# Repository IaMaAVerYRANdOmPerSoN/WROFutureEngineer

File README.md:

# WRO 2026 Future Engineers – TEAM APOSTLA

## Project Overview
This repository contains the complete documentation, code, design files, and test records for our **WRO 2026 Future Engineers** self-driving car project.

This repo is organized to show:
- how our robot is mechanically designed
- how power and sensors are arranged
- how the software is structured
- how engineering decisions were made
- how another team could reproduce the robot

---

## Team Members

<p align="center"><i>Explorer Robotics — WRO Future Engineers 2026</i></p>

---

We are a three-person team from Explorer Robotics in Whitby, Ontario, Canada. We have been competing in WRO for several years. This year we set out to build a fully autonomous self-driving robot from scratch, designing our own chassis, differential gear system, and vision pipeline.

## Elvis Wang
<table>
<tr>
  <td align="center" width="40%">
    <br>
    <em>Elvis</em>
  </td>

  <td valign="top" width="60%">

  ### Information
  - *I love building!!!!!!!*
  - 15 years old
  - Hi, my name is Elvis. I'm 15. I enjoy building and 3D modeling various objects with Fusion 360. I've been with Explorer Robotics ever since I was 8 years old.
  </td>
</tr>
</table>

---

## Michael Xie
<table>
<tr>
  <td align="center" width="40%">
    <br>
    <em>Michael</em>
  </td>

  <td valign="top" width="60%">

  ### Information
  - *I love coding!!!!!!*
  - 14 years old
  - I'm Michael. I'm 14, love coding and solving problems. I've been involved in WRO for several years and enjoy using my programming skills to help our team build and improve our robot.
  </td>
</tr>
</table>

---

## Ryan Rao
<table>
<tr>
  <td align="center" width="40%">
    <br>
    <em>Ryan</em>
  </td>

  <td valign="top" width="60%">

  ### Information
  - *I love dogs*
  - 15 years old
  - Hi! I'm Ryan. I'm 15, love to write, play badminton, listen to music, and travel. I've been involved in robotics for nearly a decade and participated in both FLL and WRO Robo Mission.
  </td>
</tr>
</table>

## Coach Rice
<table>
<tr>
  <td align="center" width="40%">
    <br>
    <em>Coach Rice</em>
  </td>

  <td valign="top" width="60%">

  ### Information
  - Head coach of Robotics Competitions, including FLL (First LEGO League),  WRO (World Robotics Olympiad) Robo Sports, Future Engineers, and Robo Mission. Led teams in winning multiple national, international robotics, and programming awards.
  - Over 20 years of IT industry experience as a software engineer working internationally.
  - MSc in Electrical & Computer Engineering from the University of Alberta.
  - BSc in Mathematics from Peking University.
  - Founder of Explorer Robotics, a local robotics club in Ajax and Whitby, teaching coding, AI, robotics, etc.
  </td>
</tr>
</table>

---

## Robot Summary

> Our robot is a self-driving car built for the WRO 2026 Future Engineers challenge. It uses one downward-angled camera to spot track walls, corner lines, and colored obstacle pillars, and follows the track using a state-machine control loop. The robot runs on a Raspberry Pi 5 for vision, an Arduino Nano for motor and servo control, a Furitek Micro Komodo 1212 brushless motor that drives the rear wheels through a differential gearbox, and rack-and-pinion steering run by an HS-5055MG servo. Our design is simple and reliable, using one sensor for all detection and a sturdy build that's easy to fix during competition.

---

## Journal
- [View Journal](docs/journal/CHANGELOG.md)
- [View Journal PDF](docs/journal/CHANGELOG.pdf)

---

## Table of Contents

- [Project Overview](#project-overview)
- [Team Members](#team-members)
- [Robot Summary](#robot-summary)
- [Repository Structure](#repository-structure)
  - [Main Files](#main-files)
  - [Documentation](#documentation)
  - [Other Project Assets](#other-project-assets)
- [1. Mechanical Design](#1-mechanical-design)
  - [Images of Robot](#images-of-robot)
  - [Structural Design](#structural-design)
    - [Old Design](#old-design)
    - [Improvements](#improvements)
    - [Changes](#changes)
  - [3D Printed Parts](#3d-printed-parts)
  - [Full Robot](#full-robot)
- [2. Power and Sensor Architecture](#2-power-and-sensor-architecture)
  - [Power](#power)
  - [Voltage and Current Requirements](#voltage-and-current-requirements)
    - [5V Rail (Raspberry Pi, Arduino, Servo)](#5v-rail-raspberry-pi-arduino-servo)
    - [7.4V Rail (Motor)](#74v-rail-motor)
    - [Total Battery Power and Current](#total-battery-power-and-current)
    - [Runtime Estimate](#runtime-estimate)
  - [Sensors](#sensors)
  - [Compute](#compute)
  - [Summary](#summary)
- [3. Software Architecture and Strategy](#3-software-architecture-and-strategy)
  - [Software](#software)
  - [Architecture](#architecture)
  - [Config](#config)
  - [Vision](#vision)
    - [Wall Following](#wall-following)
    - [Obstacle Detection](#obstacle-detection)
  - [Hardware Interfaces](#hardware-interfaces)
  - [Challenge Running](#challenge-running)
    - [Open Challenge](#open-challenge)
    - [Obstacle Challenge](#obstacle-challenge)
  - [Running the Robot](#running-the-robot)
- [4. Systems Engineering and Design Decisions](#4-systems-engineering-and-design-decisions)
  - [Constraints](#constraints)
  - [Trade-offs](#trade-offs)
  - [Design Iteration](#design-iteration)
  - [Risk Analysis](#risk-analysis)
  - [Subsystem Interactions](#subsystem-interactions)
  - [Summary](#summary-1)
- [5. Reproducibility](#5-reproducibility)
  - [Software Setup](#software-setup)
  - [Hardware Setup](#hardware-setup)
  - [Testing](#testing)
  - [Summary](#summary-2)
- [Testing and Validation](#testing-and-validation)
- [Media and Visual Documentation](#media-and-visual-documentation)
  - [Diagrams](#diagrams)
  - [Videos](#videos)
- [CAD and Wiring Files](#cad-and-wiring-files)
- [Version History](#version-history)
- [Contribution and Documentation Rules](#contribution-and-documentation-rules)
- [Final Notes](#final-notes)
- [View Journal](docs/journal/CHANGELOG.md)

---
### GitHub Releases
[GitHub releases page](https://github.com/IaMaAVerYRANdOmPerSoN/WROFutureEngineer/releases/tag/v0.1.0)
- Source Code
- Cad File

---

## Repository Structure

### Main Files
- `README.md` – main project overview and navigation
- `LICENSE` – repository license
- `.gitignore` – ignored local/generated files
- `requirements.txt` – Python dependencies

### Documentation
- `docs/01_mechanical/` – mobility and mechanical design
- `docs/02_power_sensors/` – power system and sensor architecture
- `docs/03_software/` – software design and obstacle strategy
- `docs/04_systems_engineering/` – engineering decisions, trade-offs, and risks
- `docs/05_reproducibility/` – build, setup, assembly, and testing workflow
- `docs/journal/` – dated engineering journal (Markdown + PDF export)
- `docs/img/` – images referenced throughout the docs (robot photos, diagrams, team photos)
- `docs/plan.md`, `docs/shoppingList.md`, `docs/coach_comments.md` – supporting planning docs

**Other top-level folders:**
- `ArudinoServer/` – PlatformIO firmware for the Arduino (low-level motor/servo control)
- `PiClient/` – Python code on the Raspberry Pi
    - `src/` – main vision processing, control, and Arduino communication logic
    - `src_min/` – a minimal/leaner variant of the same modules
    - `utils/tools/` – standalone calibration and debug tools (contours, manual control)
    - `tests/` – test and experiment scripts
- `EDA/` – KiCad PCB project 
    - `FAB/` – fabrication outputs (Gerbers, BOM, pick-and-place positions)
    - `lib/` – imported component symbol/footprint libraries

---

# 1. Mechanical Design
This section explains the physical design of the robot, including chassis layout, steering, drivetrain, torque/speed reasoning, and mechanical improvements over time.

---

### Files
- [`docs/mechanical/mechanical_reasoning.md`](docs/01_mechanical/mechanical_reasoning.md)
- [`docs/mechanical/mechanical_iterations.md`](docs/01_mechanical/mechanical_iterations.md)
- [`docs/mechanical/torque_speed_reasoning.md`](docs/01_mechanical/torque_speed_reasoning.md)

---

- **Dimentions**: 24cm length 10cm wide 28cm high
    - [Dimentions reasoning](docs/01_mechanical/mechanical_reasoning.md#size-reasoning)
- **Drive Motor**: Furitek Micro Komodo 1212 Stepper Motor
    - [Motor reasoning](docs/01_mechanical/mechanical_reasoning.md#motor-selectionmotor-selection)
- **Steering Motor**: HS-5055MG 11.9g Metal Gear Digital Micro Servo
    - [Steering reasoning](docs/01_mechanical/mechanical_reasoning.md#servo-motor)

### Images of Robot
| | |
|:---:|:---:|
|  |  |
|  |  |
|  |  |

---

- **Drive System**: We use rear wheel drive, means the motor's power is transmitted to the back wheels rather than the front.
    - [Why RWD?](docs/01_mechanical/mechanical_reasoning.md#drive-system)
- **Steering type:** Parallel (Zero-Ackermann), Both front wheels turn at the same angle instead of the inner wheel turning more sharply than the outer. It does cause slight tire scrub during turns but it is acceptable on a small lightweight robot on a smooth mat.
    - [Why Parallel Zero-Ackermann?](docs/01_mechanical/mechanical_reasoning.md#steering-system)
### Structural Design
To get our current design, we took inspiration from our previous robot we used last year in Future Engineers.

#### Old Design

#### Improvements
- Make the robot thinner for more clearence and better weight distribution
- More supports on the sides of the robot (we only had 2)

---

#### Changes
- Rotating the Raspiberry Pi 90 degrees would allow for a slimmer design
- Implimenting more supports on the sides of the robot
- We use the Arduino Nano instead of Hiwonder
- Changed the camera angle and added a place for the stepdown voltage

### 3D Printed Parts

- **Turning System**: Servo-actuated rack and pinion steering with a curved front bumper for wall sliding in the obstacle challenge. The servo connects to the steering rack via a servo horn and tie rods, rotating the servo horn pushes or pulls the tie rods, which turn the front wheels left or right.
    - [Turning system iterations](docs/01_mechanical/mechanical_iterations.md#turning-system)

- **Raspberry Pi 5 Layout, Camera Mount, and ESC**: Slim rotated design with a separated camera tower angled at 35 degrees downward. The ESC is mounted inside the same assembly to keep electronics consolidated.
    - [RP5 layout and camera mount iterations](docs/01_mechanical/mechanical_iterations.md#raspberry-pi-5-layout-and-camera-mount)

- **Arduino Nano Layout**: Main chassis plate holding the Arduino, servo, and front assembly; redesigned for compactness across four versions
    - [Arduino layout iterations](docs/01_mechanical/mechanical_iterations.md#europe-design)

- **Connectors**: 3D printed C-shaped connectors replacing brass standoffs to speed up assembly and disassembly
    - [Connector iterations](docs/01_mechanical/mechanical_iterations.md#connectors)

- **Furitek Micro Komodo 1212**: Brushless motor rated at 3450 KV and 120W; drives the rear wheels through the differential gearbox
    - [Motor reasoning](docs/01_mechanical/mechanical_reasoning.md#motor-selection)

- **Differential Gear System**: Custom-designed differential allowing the rear wheels to spin at different speeds during turns; went through multiple iterations before settling on an off-the-shelf gearbox

- **Wheels**: 35mm rubber wheels chosen to raise the chassis to give the differential adequate ground clearance
    - [Wheel and torque reasoning](docs/01_mechanical/torque_speed_reasoning.md)

- **Ball Bearings**: Four 6mm ball bearings pressed into the rear body mount to support the axles and reduce friction

---

### Full Robot

| | |
|:---:|:---:|
|  |

---

### Assembly Video

---

# 2. Power and Sensor Architecture
This section explains how the robot is powered, what sensors are used, where they are placed, and how they are calibrated.

### Files
- [`docs/02_power_sensors/power_architecture.md`](docs/02_power_sensors/power_architecture.md)
- [`docs/02_power_sensors/sensor_selection.md`](docs/02_power_sensors/sensor_selection.md)
- [`docs/02_power_sensors/sensor_placement.md`](docs/02_power_sensors/sensor_placement.md)
- [`docs/02_power_sensors/calibration.md`](docs/02_power_sensors/calibration.md)

---

### Power

Everything starts with a single Gens Ace 1300mAh 2S LiPo battery. From there, power splits into two separate paths so the compute side and the actuator side never interfere with each other.

The first path goes through our Yahboom voltage regulator board, which steps the battery's 7.4V down to a clean 5V. That 5V feeds into the Raspberry Pi 5 through USB-C. The Arduino Nano doesn't connect to the battery at all, it gets powered straight from the Pi over a USB-B cable. The camera is also powered off the Pi, through its flat CSI ribbon cable, which carries both data and power in one connector.

The second path runs through the ESC. The ESC takes power directly from the battery and has its own built-in BEC (battery eliminator circuit) to regulate it. On the output side, the ESC's voltage pin powers the servo, and the ESC also drives the brushless motor directly since the motor doesn't need to be stepped down first.

<p align="center"><i>Full electronics schematic showing power distribution and signal connections.</i></p>

The Raspberry Pi is the brain, it runs the vision pipeline, figures out where objects are, and decides what the robot should do next. The Arduino doesn't make any decisions, it just takes the drive commands the Pi sends it and turns them into precise PWM signals, since the Pi can't reliably time PWM output on its own while it's busy processing frames. The camera is the robot's only sense of the outside world, it feeds every frame the vision pipeline uses to find walls, corners, and pillars.

On the actuator side, the ESC handles throttle control for the drive motor based on the PWM signal it gets from the Arduino, and its BEC also acts as the power source for the servo, so the servo never has to touch the battery directly. The servo itself just turns the front wheels left and right based on the steering commands coming from the Arduino, and the motor is what actually moves the robot forward, spinning the rear wheels through the differential.

- **Battery**: Gens Ace 1300mAh 2S LiPo, 7.4V nominal, 45C discharge
    - [Battery details](docs/02_power_sensors/power_architecture.md#battery)
- **Voltage Regulation**: Yahboom regulator converts 7.4V to 5V for the Raspberry Pi; ESC built-in BEC powers the servo independently
    - [Regulator details](docs/02_power_sensors/power_architecture.md#design-rationale)
- **Main Power Switch**: Smaller switch installed on the main battery rail after the original 20A switch was replaced for easier integration
    - [Power design](docs/02_power_sensors/power_architecture.md#iterations)
- **Estimated Runtime**: ~17 minutes at average load; enough for ~5 full competition runs per charge

## Voltage and Current Requirements

### 5V Rail (Raspberry Pi, Arduino, Servo)

| Component | Current Draw |
|-----------|-------------|
| Raspberry Pi 5 | 2.40A |
| Arduino Nano | 0.05A |
| Servo Motor (stall) | 0.70A |
| Camera (OV5647) | 0.25A |
| **Total 5V current** | **3.40A** |

Power at 5V: 3.40A × 5V = **17W**

Accounting for regulator efficiency (80%):
17W ÷ 0.8 = **21.25W** needed from battery for the 5V rail.

---

### 7.4V Rail (Motor)

| Component | Current Draw |
|-----------|-------------|
| Drive Motor (average during run) | 3.50A |
| **Total motor current** | **3.50A** |

Power at 7.4V: 3.50A × 7.4V = **25.9W**

---

### Total Battery Power and Current

| Rail | Power |
|------|-------|
| 5V rail (via regulator) | 21.25W |
| Motor rail (direct) | 25.9W |
| **Total** | **47.15W** |

Total current from battery:
47.15W ÷ 7.4V = **6.37A**

---

### Runtime Estimate

6.37A average draw from a 1300mAh (1.3Ah) battery at 80% usable capacity:

(1.3Ah × 0.8) ÷ 6.37A = **~0.16 hours (~10 minutes)**

In practice the robot lasts significantly longer because:
- The motor draws far less than stall current at competition speeds (30-40% throttle)
- The Raspberry Pi rarely hits full load simultaneously with peak motor draw
- The servo is at stall current only momentarily during sharp turns
- The regulator efficiency is typically closer to 85-90% under real load

At realistic average loads (~4A total), the expected runtime is approximately **17 minutes**, sufficient for ~5 full competition runs per charge.

Because of the decently short battery life, we have had between 4-5 batteries.

---

### Sensors

- **Camera (OV5647)**: Detects walls, corner lines, and colored pillars via CSI-2 at 640x480 up to 62.50 fps
    - [Camera selection](docs/02_power_sensors/sensor_selection.md#camera--ov5647)
    - [Camera placement](docs/02_power_sensors/sensor_placement.md)
- **IMU**: Detects rotation and acceleration
    - [IMU purpose](docs/02_power_sensors/sensor_selection.md#camera--ov5647)
      
---

### Compute

- **Raspberry Pi 5 (8GB)**: Main compute unit running the vision pipeline, control loop, and Arduino communication
    - [Raspberry Pi details](docs/02_power_sensors/sensor_selection.md#raspberry-pi-5-8gb)
- **Arduino Nano**: Handles PWM output to ESC and servo; receives drive commands from the Pi over USB serial
    - [Arduino details](docs/02_power_sensors/sensor_selection.md#arduino-nano)

---

### Actuators

- **ESC**: Furitek Lizard Pro 30A/50A ESC
    - [ESC reasoning](docs/02_power_sensors/power_architecture.md#electronic-speed-controller)
- **Drive Motor**: Furitek Micro Komodo 1212 Stepper Motor
    - [Motor reasoning](docs/01_mechanical/mechanical_reasoning.md#motor-selectionmotor-selection)
- **Steering Motor**: HS-5055MG 11.9g Metal Gear Digital Micro Servo
    - [Steering reasoning](docs/01_mechanical/mechanical_reasoning.md#servo-motor)
---

## Risks and Mitigation

- **Voltage drop:** The 45C discharge rating minimizes voltage sag under peak current draw. Battery voltage is monitored during practice runs to identify cell degradation early.
- **Brownout:** The Pi is powered through a Yahboom voltage regulator board rather than directly from the battery, isolating it from motor-induced voltage dips. A regulator with sufficient headroom above the Pi's peak draw was selected. We may have broken one of our raspberry pi's because we forgot the regulator...
- **Electrical noise:** Motor and ESC wiring are routed away from signal wires. The serial communication lines between the Pi and Arduino are kept short.
- **Loose connectors:** All connectors are secured with heat shrink. Once, one of our wires got caught in the gear system causing damage, leading to a short circuit. All wiring has since been replaced.
- **Overheating:** The ESC and motor are mounted with airflow clearance. Competition runs are under 3 minutes, well within thermal limits. The Raspberry Pi fan is configured to always run after the temperature sensor proved unreliable on our unit.
- **Power spikes from motors / servos:** The ESC BEC powers the servo independently from the motor rail. The dedicated regulator for the Pi prevents motor spikes from reaching the compute system.

---

### Summary
- battery: Gens Ace 1300mAh 2S LiPo (7.4V, 45C)
- voltage regulation: Buck regulator for Pi (5V); ESC BEC for servo
- main sensors: OV5647 camera (CSI-2)
- sensor placement strategy: Camera mounted at front with downward tilt for field of view
- calibration approach: HSV color thresholds tuned under competition lighting using interactive tuning tools in `utils/`

---

# 3. Software Architecture and Strategy

## Software

This section explains the software that runs on the Raspberry Pi, including how the processes are structured, how the robot detects walls and obstacles, and how drive commands are sent to the Arduino.

---

### Files
- [`docs/03_software/architecture.md`](docs/03_software/architecture.md)
- [`docs/03_software/challenge)running.md`](docs/03_software/challenge_running.md)
- [`docs/03_software/config.md`](docs/03_software/config.md)
- [`docs/03_software/hardware_interfaces.md`](docs/03_software/hardware_interfaces.md)
- [`docs/03_software/state_machine.md`](docs/03_software/state_machine.md)
- [`docs/03_software/vision.md`](docs/03_software/vision.md)

---

## Architecture

Three processes run at the same time, camera, vision, and main control. The camera writes frames into shared memory, the vision process reads them and finds walls and obstacles, and the main process runs the state machine and sends commands to the Arduino. The system always uses the freshest data; stale frames and commands are dropped automatically.

- **Camera Process**: Captures frames and writes them into shared memory
    - [Architecture details](docs/03_software/architecture.md)
- **Vision Process**: Reads frames and finds walls and obstacles
    - [Vision details](docs/03_software/vision.md)
- **Main Process**: Runs the state machine and sends drive commands to the Arduino
    - [Runner details](docs/03_software/challenge_running.md)

<p align="center"><i>Full software architecture diagram.</i></p>

---

## Config

All settings are stored in `piclient.toml`. Nothing is hardcoded — speed, PD gains, HSV thresholds, serial ports, and ROI sizes are all in the config file. Once the robot starts, the config is locked and cannot be changed mid-run.

- **Settings file**: `piclient.toml` at the root of the repo
    - [Config details](docs/03_software/config.md)
- **Override priority**: CLI flag > environment variable > `piclient.toml` > code defaults

---

## Vision

### Wall Following

`open_challenge.py:95-104` the vision pipeline counts the number of black pixels in the left, right, and center regions of the image. The difference between right and left distance is fed into a PD controller (`wall_follow.tick(right - left)`), and the output is sent as a steering command via `client.drive_motors(...)`. If the right wall is further than the left, the correction steers left, and vice versa. It only cares about relative position, not absolute distance, which is why the perspective transform can be skipped. Camera distortion does not change which wall is closer.

### Obstacle Detection

`vision_processing.py:100-106`: red and green pillars are found the same way as walls, but contours (as NumPy arrays) are used instead of simple pixel counts. Once a pillar is found, `_get_target` calculates a target x position by offsetting the pillar's x position proportionally to the width of the pillar. A separate PD controller (`obstacle_avoid`) steers toward that target x position rather than centering between walls, while maintaining 20% wall-follow weight to keep general awareness. This only runs in `obstacle_challenge.py`'s "obstacle_avoid" state, and only when `obstacles` is non-empty. Otherwise, it falls back to plain wall following.

- **Open Challenge**: Counts black pixels in left, right, and center regions. More black pixels means the wall is closer. Corner detection triggers when the center region fills up.
    - [Open challenge vision details](docs/03_software/vision.md#open-challenge)
- **Obstacle Challenge**: Finds red and green pillars using HSV color detection and calculates an offset target x position to steer toward the gap between the pillar and the wall.
    - [Obstacle challenge vision details](docs/03_software/vision.md#obstacle-challenge)

---

## Hardware Interfaces

- **Camera**: Runs in its own process, writes frames directly into shared memory with no copying
    - [Camera details](docs/03_software/hardware_interfaces.md#camera)
- **Arduino Client**: Sends serial commands with transaction IDs so multiple commands can be in flight at once
    - [Arduino client details](docs/03_software/hardware_interfaces.md#arduino-client)
- **DriveCommandExecutor**: Sits between the control loop and the Arduino, only the latest command is sent, stale commands are thrown away
    - [DriveCommandExecutor details](docs/03_software/hardware_interfaces.md#drivecommandexecutor)

---

## Challenge Running
The robot uses a finite state machine (FSM) to decide what to do at any given moment. Each state has a specific trigger that causes the robot to enter it and a specific action it takes while in that state. The FSM runs once per camera frame, so the robot is constantly re-evaluating which state it should be in based on the latest vision data.

### Open Challenge

| State | Trigger | Action |
|-------|---------|--------|
| Straight | Default | Wall follow with PD controller |
| Turn | Black fill detected ahead | Hard steer toward missing wall |
| Final Turn | Last turn of last lap | Same as Turn |
| Final Straight | After final turn | Drive to stop |

- [Open challenge runner details](docs/03_software/challenge_running.md#open-challenge)

### Obstacle Challenge

| State | Trigger | Action |
|-------|---------|--------|
| Straight | Default | Wall follow with PD controller |
| Turn | Corner detected | Hard steer toward missing wall |
| Obstacle Avoid | Vision returns a pillar target | Steers toward the gap between pillar and wall |
| Parallel Parking | Vision returns a parking lot target and the 3rd lap is complete | Steers toward the parking lot and executes a parallel parking maneuver |

Same as the open challenge with one extra state. When a pillar is detected, the robot steers toward the gap between the pillar and the wall. Green pillars are passed on the left, red on the right.

- [Obstacle challenge runner details](docs/03_software/challenge_running.md#obstacle-challenge)

---

## Running the Robot

```bash
wro --GeneralConfig.CHALLENGE open
wro --GeneralConfig.CHALLENGE obstacle
```

Full auto-generated API docs: https://apostla-api-reference.web.app/
---

# 4. Systems Engineering and Design Decisions
This section explains how the robot was developed as an integrated system and how trade-offs were evaluated.

- **Engineering Journal**:
The journal is best viewed on GitHub where all links are clickable. A PDF version is also available for submission.
    - [View Journal](docs/journal/CHANGELOG.md)
    - [View Journal PDF](docs/journal/CHANGELOG.pdf)

### Files
- [`docs/04_systems_engineering/subsystem_interactions.md`](docs/04_systems_engineering/subsystem_interactions.md)
- [`docs/04_systems_engineering/constraints_tradeoffs.md`](docs/04_systems_engineering/constraints_tradeoffs.md)
- [`docs/04_systems_engineering/risk_analysis.md`](docs/04_systems_engineering/risk_analysis.md)
- [`docs/04_systems_engineering/iteration_cycles.md`](docs/04_systems_engineering/iteration_cycles.md)

### Constraints

The robot must satisfy four levels of constraints in order of priority:

- **WRO rules compliance**: Size, mass, power, and mechanical limits must be respected at all times. The robot must start, stop, and reset reliably.
- **Score maximization**: The robot must complete challenge objectives as reliably as possible, minimize recovery time, and avoid oscillations and false detections.
- **Simplicity and reliability**: Each subsystem has a clear single purpose. The system degrades gracefully under sensor noise and is easy to debug during competition setup.
- **Speed**: The camera pipeline, control loop, and serial interface must keep up with the required frame rate without creating stale-data backlogs.
    - [Full constraint tree](docs/04_systems_engineering/constraints_tradeoffs.md#constraint-tree)

---

### Trade-offs

Trade-offs are evaluated against the constraint hierarchy, a trade-off that violates a higher-level constraint is rejected regardless of its other benefits. Hardware trade-offs are treated with more caution than software trade-offs because they are harder to reverse. A quick preliminary solution is always tested on the track before committing to a final design.

- **Single camera over multiple sensors**: Reduces weight, cost, and synchronization complexity. HSV calibration and track testing address the lighting sensitivity limitation.
- **Rear-wheel drive over four-wheel drive**: Simpler drivetrain leaves more room for reliable software and testing.
- **Latest-wins command scheduling**: A fresh steering correction is more valuable than guaranteed delivery of an outdated command.
- **Namespace package architecture**: More complex to set up but provides clear interfaces, independent distribution, and sustainable long-term maintainability.
    - [Full trade-off analysis](docs/04_systems_engineering/constraints_tradeoffs.md#trade-offs)

---

### Design Iteration

Major design decisions are modelled as a Directed Acyclic Graph, early hardware choices form root nodes that constrain downstream software and tuning decisions. Two case studies show how this plays out in practice:

- **Differential gear**: Five iterations from an adapted GrabCAD design through three custom printed versions to a salvaged RC gearbox. Each iteration exposed a new constraint, material limits, tolerance stacking, component sizing, that drove the next architectural shift.
- **Python packaging**: Four iterations from a flat src directory to a namespace package architecture with independently distributable components, driven by the need for clear interfaces between the camera, vision, control, and recording subsystems.
    - [Full iteration history](docs/04_systems_engineering/iteration_cycles.md)

---

### Risk Analysis

Risks are identified through track telemetry, SPICE circuit simulation, and rulebook audits. Each risk is placed on a likelihood vs. impact matrix to prioritize fixes. Mitigation follows the same iterative process as design, a quick patch is tested on the track first, then refined into the final solution.

- **Risk lifecycle**: Identify → Evaluate → Mitigate → Validate on track → Iterate
    - [Full risk analysis](docs/04_systems_engineering/risk_analysis.md)

---

### Subsystem Interactions

The robot's performance is determined by how its subsystems work together. Key interactions:

- **Mechanical and control**: Steering range, drive speed, camera height, and PD gains must be tuned together, a software improvement is only useful if the drivetrain can produce the requested response.
- **Power and electrical**: Motor and servo current spikes can cause Raspberry Pi brownouts. The regulator and wiring separate high-current actuator loads from compute power.
- **Perception and behavior**: The camera is the only active sensor. Vision runs in a separate process and signals the main loop when fresh data is ready. Corner detection requires several consecutive frames to filter noise.
- **Software and communication**: The DriveCommandExecutor uses latest-wins scheduling so serial latency never creates a backlog of stale commands.
    - [Full subsystem interaction map](docs/04_systems_engineering/subsystem_interactions.md)

---

### Summary
- biggest engineering constraints: WRO size and mass limits; camera-only perception under variable lighting; PLA material limits for 3D printed gears
- main trade-offs: Single camera vs. multi-sensor; RWD vs. AWD; namespace packages vs. flat src; printed differential vs. off-the-shelf gearbox
- most important decisions: Latest-wins command scheduling; parallel process architecture; namespace package distribution
- major risks: Differential gear failure; Raspberry Pi brownout; camera detection failure under competition lighting
- how the robot improved through iteration: Each failure exposed a new constraint that drove the next design, five differential versions, four packaging versions, and continuous PD and HSV tuning on the track

---

# 5. Reproducibility
This section explains how another team could rebuild, set up, and test the robot.

### Files
- [`docs/05_reproducibility/build_guide.md`](docs/05_reproducibility/build_guide.md)
- [`docs/05_reproducibility/bill_of_materials.md`](docs/05_reproducibility/bill_of_materials.md)
- [`docs/05_reproducibility/setup_guide.md`](docs/05_reproducibility/setup_guide.md)
- [`docs/05_reproducibility/building_from_source.md`](docs/05_reproducibility/building_from_source.md)
- [`docs/05_reproducibility/testing_workflow.md`](docs/05_reproducibility/testing_workflow.md)
- [`docs/05_reproducibility/release_notes.md`](docs/05_reproducibility/release_notes.md)

---

### Software Setup

- **Normal install**: Install the prebuilt wheel using pip on Raspberry Pi OS (64-bit, Bookworm or later)
    - [Setup guide](docs/05_reproducibility/setup_guide.md)
- **Build from source**: Clone the repo and build four namespace packages using Python 3.13+. Required if the wheel is not yet published to PyPI.
    - [Building from source](docs/05_reproducibility/building_from_source.md)
- **picamera2**: Not included in the wheel — use the system-wide installation bundled with Raspberry Pi OS. Do not install from source.

```bash
python -m venv --system-site-packages .venv
source .venv/bin/activate
pip install piclient[all]
```

---

### Hardware Setup

- **Bill of materials**: Full component list including electronics, mechanical parts, 3D printed parts, and tools
    - [Bill of materials](docs/05_reproducibility/bill_of_materials.md)
- **Build Guide** How to print, assemble, and build our robot
    - [Build Guide](docs/05_reproducibility/build_guide.md)
---

### Testing

- **Track is the source of truth**: No change is considered valid until tested on the real track. Unit tests and integration tests are automated via CI/CD but cannot replace real-world validation.
- **Hardware testing**: Components are tested directly on the robot. 3D printed parts are rapidly prototyped and tested. Electronics are validated in SPICE simulation before being installed.
- **Software testing**: All pull requests are automatically tested by the CI/CD pipeline. Logs and video footage are used to diagnose failures.
- **Fallback plan**: Spare parts are kept for all critical components. All packages are versioned and uploaded to PyPI for quick rollback. A fully assembled electronics backup is kept ready for competition.
    - [Testing workflow](docs/05_reproducibility/testing_workflow.md)

---

### Summary
- how to build the robot: See bill of materials and build guide
- how to install software: `pip install piclient[all]` on Raspberry Pi OS Bookworm
- how to calibrate: Run `python -m utils --tool contours control` under competition lighting and update `piclient.toml`
- how to test: Run on track — unit tests via CI/CD, real-world validation required for all changes
- what files are needed to reproduce the system: All STL files in `models/stl/`, config in `piclient.toml`, Arduino firmware in `ArudinoServer/`

## Testing and Validation
Summarize how the robot was tested.

Example points:
- bench tests for hardware
- sensor tests
- steering tests
- lane following tests
- obstacle avoidance tests
- full track tests

Detailed records:
- [`docs/04_systems_engineering/iteration_cycles.md`](docs/04_systems_engineering/iteration_cycles.md)
 - [View Journal](docs/journal/CHANGELOG.md)

---

### Diagrams

<p align="center"><i>Full software architecture diagram.</i></p>

<p align="center"><i>Full electronics schematic showing power distribution and signal connections.</i></p>

## API Reference

Full API documentation for every package in this release is at
**[apostla-api-reference.web.app](https://apostla-api-reference.web.app/)**.

### Videos
### Open Challenge Run

### Obstacle Challenge Run

Suggested folders:
- `docs/images/`
- `docs/diagrams/`

---

## Version History

- [`Journal`](docs/journal/CHANGELOG.md)

---

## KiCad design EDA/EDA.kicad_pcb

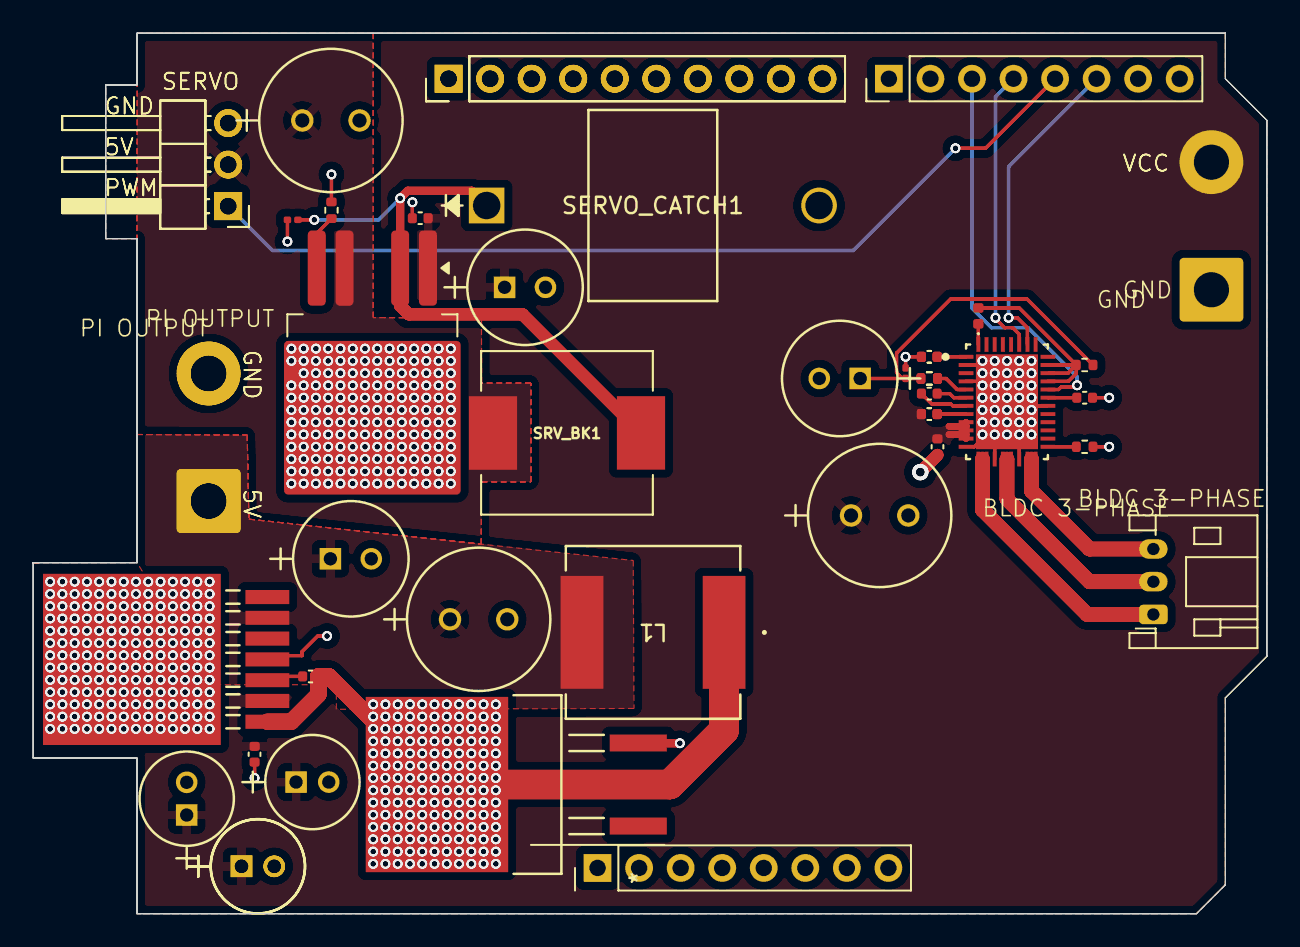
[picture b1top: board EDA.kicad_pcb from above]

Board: 2 copper layers, 75.4 x 53.8 mm, 45 parts (0 on the bottom side), 25 nets.

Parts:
ARD_A1: Conn_01x08_Pin; PinHeader_1x08_P2.54mm_Vertical
ARD_B1, ARD_B1#2: Conn_01x10_Pin; PinHeader_1x10_P2.54mm_Vertical
ARD_C1: Conn_01x08_Pin; PinHeader_1x08_P2.54mm_Vertical
AVDD_BYP1: 1uf; C_0402_1005Metric
BK_BULK1: 100uf; CAP_WCAP-ATUL_06.3X11.0_WRE
BK_BYP1: 1uf; C_0201_0603Metric
BLDC_3P1: Conn_01x03_Pin; JST_PH_S3B-PH-K_1x03_P2.00mm_Horizontal
BULK_VM2: 470uf; CAP_YX_8X11P5_RUB
BYP_SRV1: 1uf; C_0402_1005Metric
BYP_VM1: 1uf; C_0402_1005Metric
CP_HL1: 47nf; C_0402_1005Metric
C_BOOST1: 0.01uf; C_0402_1005Metric
C_PUMP1, C_PUMP1#2: 1uf; C_0402_1005Metric
DVDD_BYP1, DVDD_BYP1#2: 1uf; C_0402_1005Metric
D_FAULT1: LED; LED_0402_1005Metric
FG_PU1: 5.1k; R_0402_1005Metric
J2: Screw_Terminal_01x02; SolderWire-1.5sqmm_1x02_P7.8mm_D1.7mm_OD3.9mm
L1: SRP1038WA-220M; IND_SRP1038WA-220M_BRN
M1, M1#2: Motor_Servo; PinHeader_1x03_P2.54mm_Horizontal
PD_SRV1: 5k; R_0402_1005Metric
PI_BULK1, PI_BULK1#2, PI_BULK2, PI_BULK3: 15uf; CAP_5X11_WRE
PI_BYP1: 0.47uf; C_0402_1005Metric
PI_CATCH1: Schotty Diode; DPAK_045S-M3_VIS
PI_OUT1, PI_OUT1#2: Screw_Terminal_01x02; SolderWire-1.5sqmm_1x02_P7.8mm_D1.7mm_OD3.9mm
PI_OUT2: 470uf; CAP_YX_8X11P5_RUB
PI_OUT3: 100uf; CAP_WCAP-ATUL_06.3X11.0_WRE
R1: 5.1k; R_0402_1005Metric
R_BK1, R_BK1#2: 5.1k; R_0402_1005Metric
SERVO_CATCH1: 1N5825; 1N5825_MCH
SRVOUT_BULK1: 470uf; CAP_YX_8X11P5_RUB
SRVOUT_BYP1: 1uf; C_0201_0603Metric
SRV_BK1: 68uh; IND_SPM10065VT-680M-D
SRV_BULK1: 100uf; CAP_WCAP-ATUL_06.3X11.0_WRE
U1: PMCF8316A1VRGFR; RGF0040E-IPC_A
U2: LM2596S-5; TO-263-4
U3: LM2678S-5; TS7B

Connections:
+3V3: BK_BULK1.1, BK_BYP1.1, FG_PU1.1, R_BK1.2, R_BK1#2.2
+7.5V: BULK_VM2.1, BYP_SRV1.2, BYP_VM1.2, C_PUMP1.1, C_PUMP1#2.1, J2.2, PI_BULK1.1, PI_BULK1#2.1, PI_BULK2.1, PI_BULK3.1, PI_BYP1.2, SRV_BULK1.1, U1.9 (VM), U1.10 (VM), U1.11 (VM), U2.1 (VIN), U3.2 (VIN)
GND: ARD_A1.6, ARD_A1.7, AVDD_BYP1.1, BK_BULK1.2, BK_BYP1.2, BULK_VM2.2, BYP_SRV1.1, BYP_VM1.1, DVDD_BYP1.2, DVDD_BYP1#2.2, J2.1, M1.3 (-), M1#2.3 (-), PD_SRV1.1, PI_BULK1.2, PI_BULK1#2.2, PI_BULK2.2, PI_BULK3.2, PI_BYP1.1, PI_CATCH1.3, PI_OUT1.2, PI_OUT1#2.2, PI_OUT2.2, PI_OUT3.2, R1.1, SERVO_CATCH1.2, SRVOUT_BULK1.2, SRVOUT_BYP1.2, SRV_BULK1.2, U1.2 (DGND), U1.4 (GND_BK), U1.12 (PGND), U1.15 (PGND), U1.18 (PGND), U1.26 (AGND), U1.41 (Thermal_Pad), U2.3 (GND), U3.4 (GND), U3.8 (PAD)
unnamed: ARD_C1.3, U1.28 (SPEED_WAKE)
unnamed: ARD_C1.4, U1.35 (BRAKE)
unnamed: ARD_C1.6, U1.34 (DIR)
unnamed: BLDC_3P1.1, U1.13 (OUT_A), U1.14 (OUT_A)
unnamed: BLDC_3P1.2, U1.16 (OUT_B), U1.17 (OUT_B)
unnamed: BLDC_3P1.3, U1.19 (OUT_C), U1.20 (OUT_C)
unnamed: D_FAULT1.2 (A), FG_PU1.2, U1.29 (FG), U1.30 (SDA), U1.31 (SCL)
unnamed: D_FAULT1.1 (K), U1.40 (FAULT_N)
unnamed: AVDD_BYP1.2, U1.27 (AVDD)
unnamed: C_PUMP1.2, C_PUMP1#2.2, U1.8 (CP)
unnamed: CP_HL1.1, U1.7 (CPH)
unnamed: CP_HL1.2, U1.6 (CPL)
unnamed: R1.2, U1.21 (DRVOFF)
unnamed: DVDD_BYP1.1, DVDD_BYP1#2.1, U1.1 (DVDD)
unnamed: R_BK1.1, R_BK1#2.1, U1.5 (SW_BK)
unnamed: SERVO_CATCH1.1, SRVOUT_BYP1.1, SRV_BK1.1, U2.2 (OUT)
unnamed: PD_SRV1.2, U2.5 (~ON/OFF)
unnamed: C_BOOST1.1, U3.3 (BOOST)
unnamed: C_BOOST1.2, L1.1, PI_CATCH1.2, U3.1 (SW)
PI 5V, 5A: L1.2, PI_OUT1.1, PI_OUT1#2.1, PI_OUT2.1, PI_OUT3.1, U3.6 (FB)
SRV 5V, 3A: M1.2 (+), M1#2.2 (+), SRVOUT_BULK1.1, SRV_BK1.2, U2.4 (FB)
SRV_PWM: ARD_C1.5, M1.1 (PWM), M1#2.1 (PWM)

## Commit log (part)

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2025-12-22 Inital Communication protocal with RPI as the client and Arudino as the Server.
2025-12-28 Fully function async RPC between utilising PiClient and ArudinoServer clases.
2025-12-29 Created Asyncronous wrapper for PiCamera2, Developed obstacle detection and field boundary check
    - Async Camera wrapper opened with __aenter__ and __aexit__ methods, supports fetching single live frames, buffering frames, and live IOstreaming
    - New VisionProcessor() class finds obstacles and field bondaries with a binary mask using YUV colorspace
    - VisionObject class acts a struct to easily store and access contour data following OOP conventions.
2025-12-31 Created main file and templete test file; Started working on API documentation.
2026-01-02 implemented multiprocessing with three processes; Construct obstacle avoidance logic in main loop; Flatten `AysncVisionProcessor` calls into a single method; Create tests directory and run camera uni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
    - Configured `Picamera2` with sensor and control arguments to maximize framerate
    - Reshaped planar YUV420 into 3d array of shape (Vres, Hres, 3)
    - Refactored `stream` to support multiprocessing; converted frame_yeilder into a unbound classmethod
    - Added a async mutex to `Client.__request` to mitigate potential collisions
    - Deleted arc_spline logic in favor of a simpler look ahead system
    - Added `color` attribute to `VisionObject` to identify traffic signs
2026-01-12 Refactor AsyncCamera and VisionProcessor for improved performance; update frame dimensions and enhance logging; add comprehensive analysis method; implement multiprocessing for camera and vision proc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
2026-04-03 Update platformio.ini and main.cpp to include new motor and servo libraries; Modify AsyncCamera for higher resolution and adjust CommProtocol for increased max speed; Add tests for camera functionali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
2026-04-03 Fix steering PWM definition in main.cpp; Add main entry point for vision.py
2026-04-03 Add footprints for RGF0040E components and update documentation
    - Created new footprint files for RGF0040E-IPC_C and RGF0040E-MFG in KiCAD format.
    - Established a project plan document outlining milestones and tasks for upcoming development phases.
    Add LM2678S-12 symbol and footprints to KiCAD library
    - Created a new symbol for the LM2678S-12 in the KiCAD symbol library.
    - Added three footprints (TS7B, TS7B-L, TS7B-M) for the LM2678S-12 in the KiCAD footprint library.
    - Each footprint includes detailed pad and line definitions, along with silk screen and courtyard outlines.
2026-04-03 Add No-Connect flags and add labels, create ground terminal for Raspberry Pi.
    Started Routing PCB.
    - Developed Pi 5V, 5A power supply.
    - Working on 5V, 3A servo power supply.
    - Yet to begin wiring BLDC motor controller logic.
2026-04-03 Add initial EDA project files and configuration
    - Created EDA.step file for project steps.
    - Added autosave configuration for EDA.kicad_prl with board settings, visibility options, and net inspector panel configurations.
    - Introduced lock files for PCB and schematic with hostname and username information.
    Add components table to README
    Added a table listing various components with their products and prices.
    Add new symbols and footprints for UCY2D181MHD3TN and VS-6TQ045S-M3 components
2026-04-03 Refactor logging setup in vision.py and update shared memory handling; enhance plan.md with task details and authors; clean up shoppingList.md; add ltex dictionary for spell checking; create Ryan's e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
    Fix typos in AsyncCamera and VisionProcessor classes; Fix bugs is vision test pipeline.
2026-04-03 Add STEP file for initial prototype
2026-04-03 Refactor project structure and implement asynchronous vision processing
    - Updated import paths to reflect new project structure.
    - Renamed main test function to `run_tests` for clarity.
    - Enhanced vision processing with new detection and drawing functions.
    - Added Docker support with a Dockerfile and entrypoint script.
    - Created requirements.txt for dependency management.
    - Implemented asynchronous camera handling with shared memory.
2026-04-03 Fixed rebase conflicts
2026-04-04 Fix multiprocessing logic bugs and add additional checks for laeks
2026-04-09 KISS; Created src_min without async, multiprocessing and multithreading. Also added config file to orginal code, will migrate that over to minified code aswell
2026-04-10 General bugfix
2026-04-15 Refactor configuration management and improve code consistency
    - Updated the configuration structure to use dataclasses for better organization and default values.
    - Enhanced the Camera, Client, and VisionProcessor classes to utilize the new configuration settings.
    - Improved the handling of camera settings, including format, sensor, and control configurations.
    - Refactored the OpenChallengeConfig to centralize drive speed and command duration settings.
    - Adjusted the vision processing methods to use configurable parameters for frame dimensions and color thresholds.
    - Simplified the drive motor commands in the open challenge logic to use configuration values.
2026-04-19 Implement obstacle challenge with multiprocessing and state management
2026-04-19 Refactor challenges and enhance obstacle avoidance logic
    - Updated main entry point to support selecting between open and obstacle challenges.
    - Introduced `run_obstacle_challenge` function to handle obstacle avoidance logic.
    - Modified `run_open_challenge` to include hybrid state management.
    - Enhanced vision processing to differentiate between wall and obstacle detection.
    - Added new configuration parameters for obstacle challenge speeds and behaviors.
    - Cleaned up logging for better debugging and state tracking.
2026-04-19 Update objectives.md
    Updated goals, added mechanical objectives.
2026-04-20 Refactor open challenge and vision processing code for improved readability and performance
    - Enhanced logging and error handling in open_challenge.py
    - Improved shared memory management and subprocess handling
    - Updated visionProcessing.py to use class variables for color thresholds
    - Refactored vision tests to ensure proper frame shape validation and improved logging
    - Adjusted motor control logic in open_challenge.py for better state management
    - Cleaned up code formatting and comments across multiple files for consistency
2026-04-20 Began implementation of utility and configuration tooling.
2026-04-21 Add April 2026 STEP model to CAD directory
2026-04-21 Implement new tools for vision processing and control diagnostics; add contour binary and contours visualization, and refine raw tool functionality.
2026-04-21 Add footprints for RGF0040E components and update documentation
    - Created new footprint files for RGF0040E-IPC_C and RGF0040E-MFG in KiCAD format.
    - Established a project plan document outlining milestones and tasks for upcoming development phases.
2026-04-21 Add LM2678S-12 symbol and footprints to KiCAD library
    - Created a new symbol for the LM2678S-12 in the KiCAD symbol library.
    - Added three footprints (TS7B, TS7B-L, TS7B-M) for the LM2678S-12 in the KiCAD footprint library.
    - Each footprint includes detailed pad and line definitions, along with silk screen and courtyard outlines.
    - Updated properties for reference, value, and datasheet links in the symbol and footprints.
    - Refactor schematic for clarity and readablity.
2026-04-21 Remove lock files and update workspace configuration to include EDA directory
2026-04-21 Add No-Connect flags and add labels, create ground terminal for Raspberry Pi.
2026-04-21 Started Routing PCB.
    - Developed Pi 5V, 5A power supply.
    - Working on 5V, 3A servo power supply.
    - Yet to begin wiring BLDC motor controller logic.
2026-04-21 Add initial EDA project files and configuration
    - Created EDA.step file for project steps.
    - Added autosave configuration for EDA.kicad_prl with board settings, visibility options, and net inspector panel configurations.
    - Introduced lock files for PCB and schematic with hostname and username information.
2026-04-21 Add new symbols and footprints for UCY2D181MHD3TN and VS-6TQ045S-M3 components
    - Created symbol for UCY2D181MHD3TN with properties including reference, value, footprint, and datasheet.
    - Added footprint for UCY2D181MHD3TN with dimensions and pad specifications.
    - Created symbol for VS-6TQ045S-M3 with properties including reference, value, footprint, and datasheet link.
    - Added multiple footprints for VS-6TQ045S-M3, including DPAK_045S-M3_VIS, DPAK_045S-M3_VIS-L, and DPAK_045S-M3_VIS-M with detailed specifications.
2026-04-21 Refactor logging setup in vision.py and update shared memory handling; enhance plan.md with task details and authors; clean up shoppingList.md; add ltex dictionary for spell checking; create Ryan's e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
2026-04-21 Fix typos in AsyncCamera and VisionProcessor classes; Fix bugs is vision test pipeline.
2026-04-21 set up WRO repo structure with written README, mechanical docs, and power sensor docs. Added unedited software docs, systems docs reproducibility docs.
2026-06-18 Add footprints for RGF0040E and LM2678S-12 components and update documentation
    - Created new footprint files for RGF0040E-IPC_C and RGF0040E-MFG in KiCAD format.
    - Created a new symbol for the LM2678S-12 in the KiCAD symbol library.
    - Added three footprints (TS7B, TS7B-L, TS7B-M) for the LM2678S-12 in the KiCAD footprint library.
    - Established a project plan document outlining milestones and tasks for upcoming development phases.
    - Each footprint includes detailed pad and line definitions, along with silk screen and courtyard outlines.
    - Updated properties for reference, value, and datasheet links in the symbol and footprints.
2026-06-18 Refactored main package; Moved all modules to /piclient/src/modules except __main__, __init__ , open challenge and obstacle challenge. Fixed bugs in utils and added cross platfrom compatbility for ut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
2026-06-18 Refactor objectives in objectives.md; enhance LiDAR integration in code and tools; implement async LiDAR reading and processing; add unit tests for LiDAR functionality; Move subprocess context manage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
2026-06-18 Refactor camera configuration and processing; update frame handling in AsyncCamera, VisionProcessor, and related tests; improve import structure across utility modules.
2026-06-18 Finished open challenge
2026-06-18 Add GNU General Public License v3 to the repository
2026-06-18 Added basic test code
2026-06-18 Fix links in README, enhance power architecture details, and add recent journal entries.
2026-06-19 Restructured PiClient adopting a stronger focus on packages, updated objectives, simplfied import paths, hid private members using an export deocrator and `__all__` assignment, and removed private me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
2026-06-22 Packaged everything for PyPI, simplfied workflows, and enhanced seperation of concerns. :3
2026-06-23 Force LF line terminators on all machines
